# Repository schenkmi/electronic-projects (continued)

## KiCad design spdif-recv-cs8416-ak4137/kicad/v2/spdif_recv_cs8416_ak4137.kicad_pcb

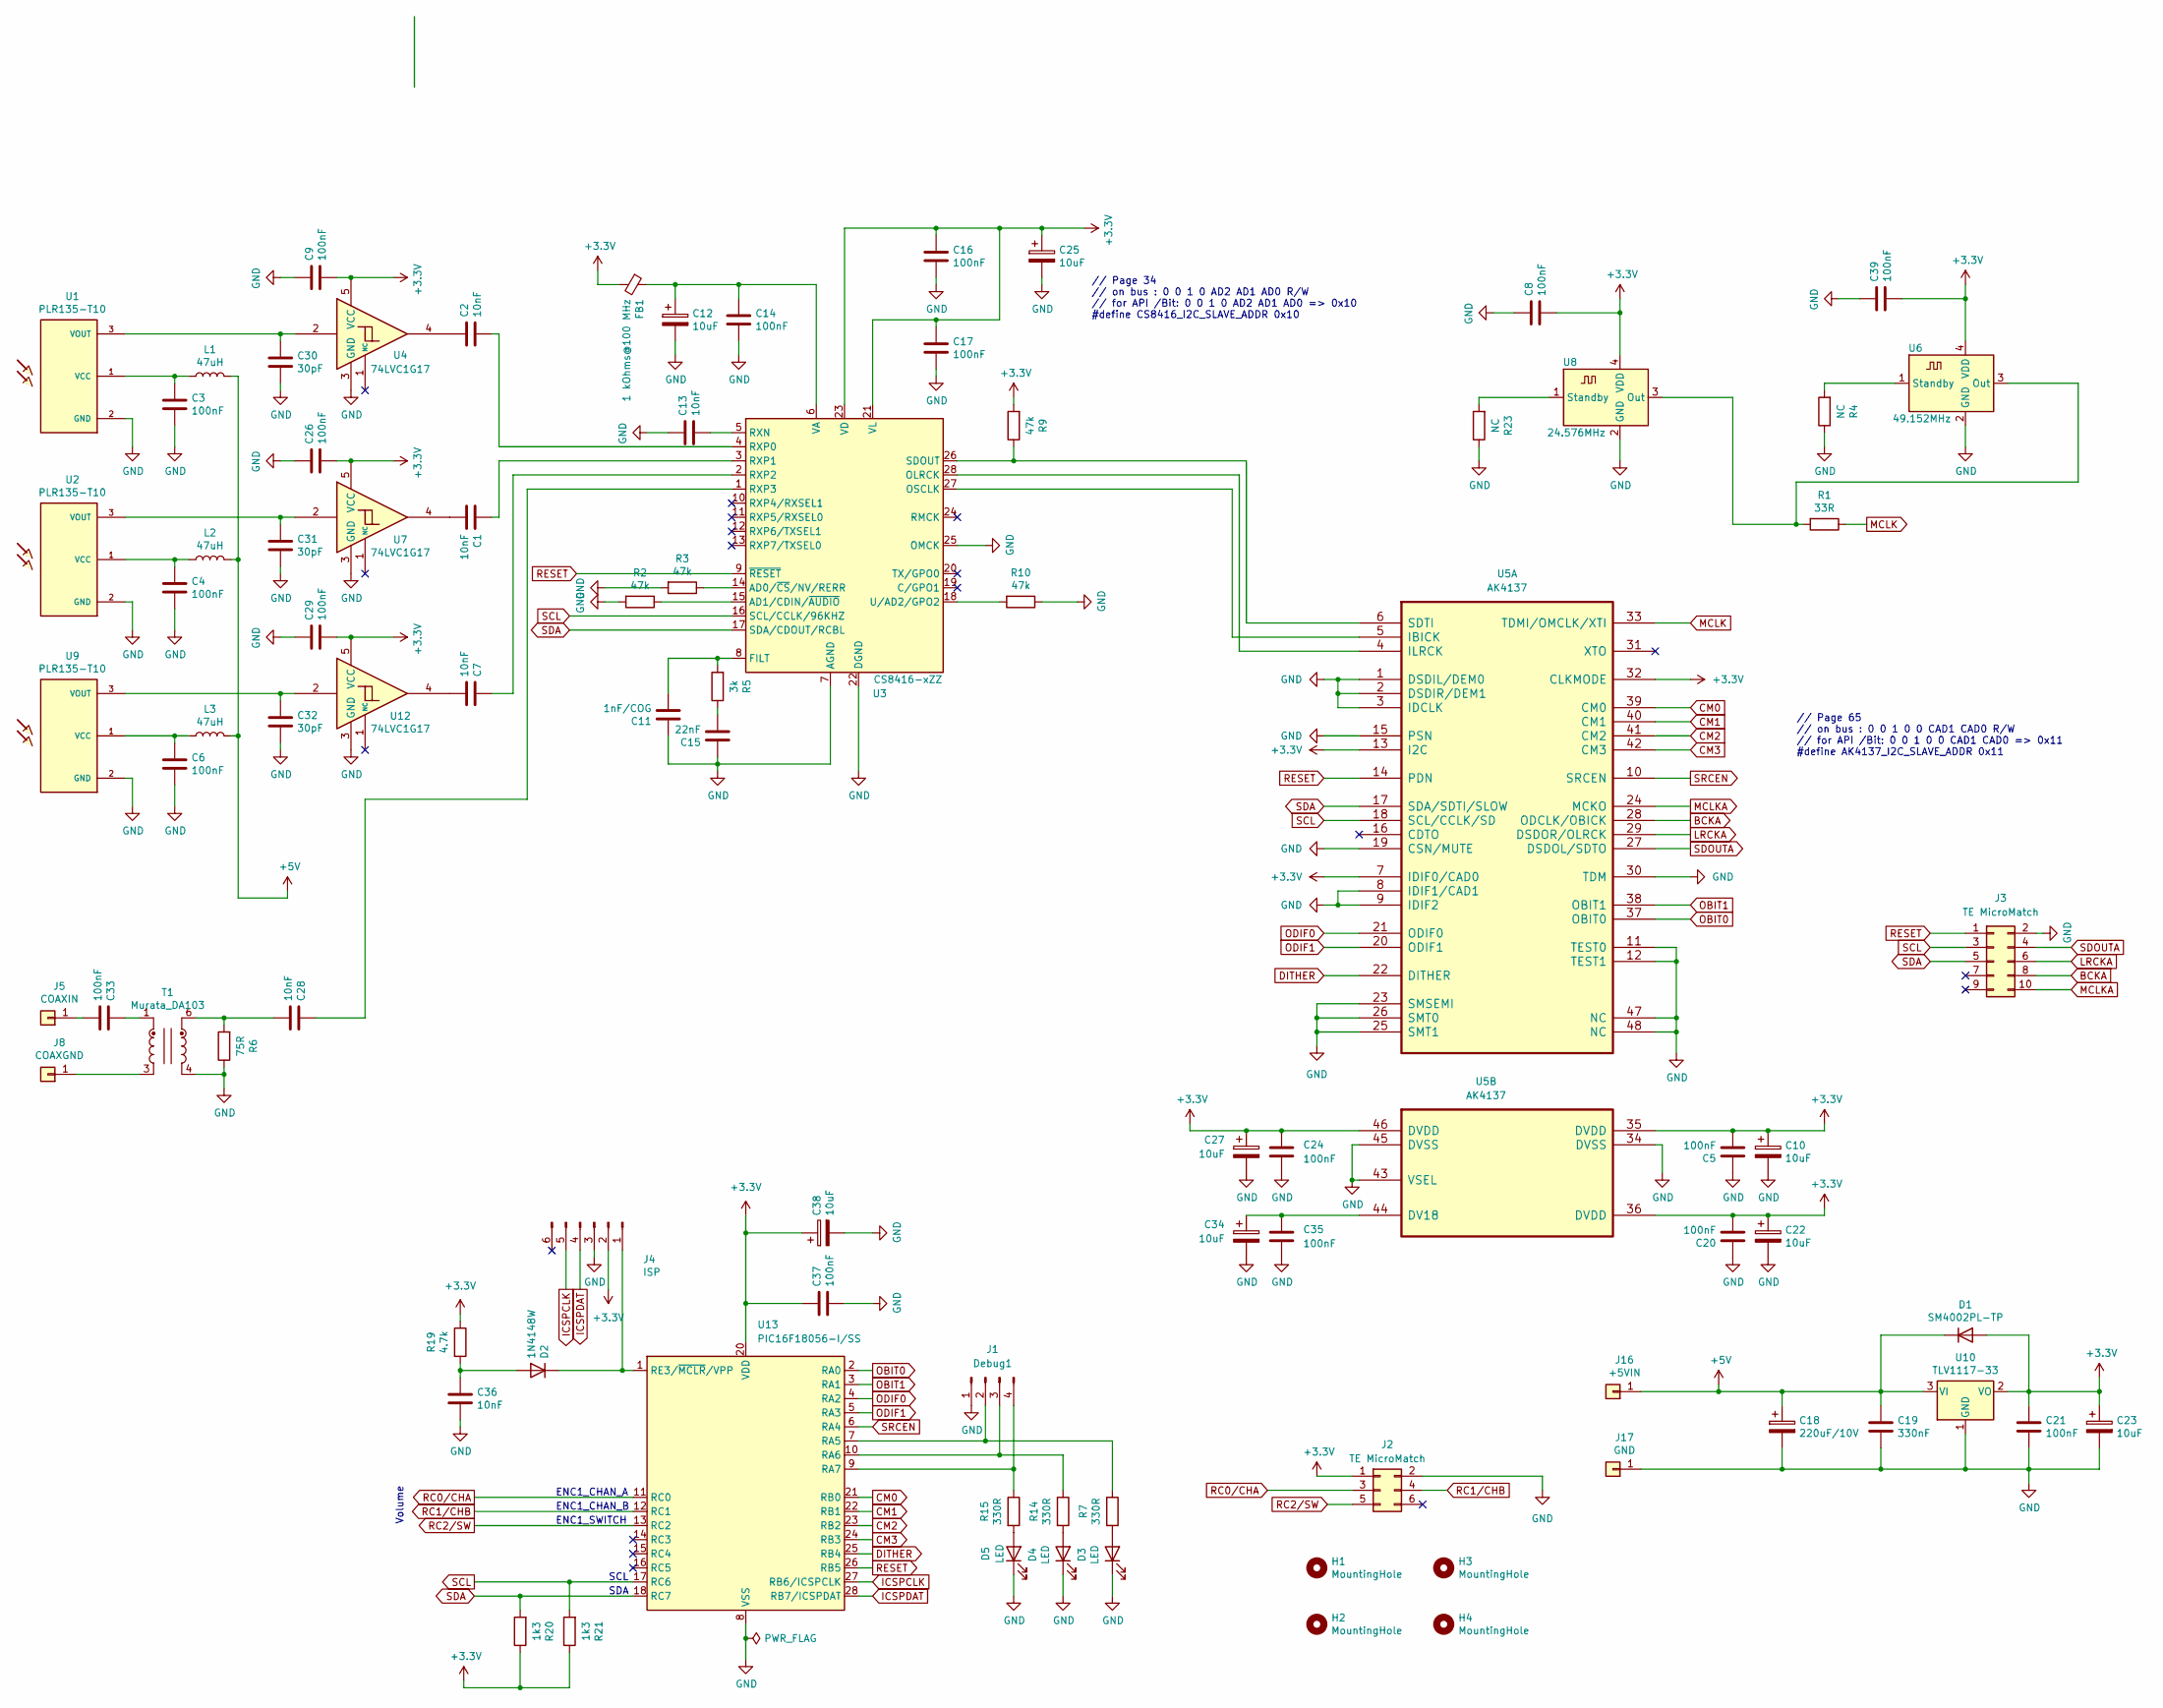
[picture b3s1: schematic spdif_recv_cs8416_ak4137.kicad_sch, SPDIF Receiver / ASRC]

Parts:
C1, C2, C7, C13, C28, C36: 10nF; C_0603_1608Metric_Pad1.08x0.95mm_HandSolder
C3, C4, C5, C6, C8, C9, C14, C16, C17, C20, C24, C26, C29, C33, C35, C37, C39: 100nF; C_0603_1608Metric_Pad1.08x0.95mm_HandSolder
C10, C12, C22, C23, C25, C27, C34, C38: 10uF; CP_EIA-2012-12_Kemet-R_Pad1.30x1.05mm_HandSolder
C11: 1nF/COG; C_0603_1608Metric_Pad1.08x0.95mm_HandSolder
C15: 22nF; C_0603_1608Metric_Pad1.08x0.95mm_HandSolder
C18: 220uF/10V; CP_Radial_D6.3mm_P2.50mm
C19: 330nF; C_0805_2012Metric_Pad1.18x1.45mm_HandSolder
C21: 100nF; C_0805_2012Metric_Pad1.18x1.45mm_HandSolder
C30, C31, C32: 30pF; C_0603_1608Metric_Pad1.08x0.95mm_HandSolder
D1: SM4002PL-TP; D_SOD-123F
D2: 1N4148W; D_SOD-123
D3, D4, D5: LED; LED_0603_1608Metric_Pad1.05x0.95mm_HandSolder
FB1: 1 kOhms@100 MHz; C_0603_1608Metric_Pad1.08x0.95mm_HandSolder
H1, H2, H3, H4: MountingHole; MountingHole_3.2mm_M3_Pad_Via
J1: Debug1; PinHeader_1x04_P2.54mm_Vertical
J2: TE MicroMatch; TE_Micro-MaTch_215079-6_2x03_P1.27mm_Vertical
J3: TE MicroMatch; TE_Micro-MaTch_1-215079-0_2x05_P1.27mm_Vertical
J4: ISP; PinHeader_1x06_P2.54mm_Vertical
J5: COAXIN; Pin_D1.0mm_L10.0mm
J8: COAXGND; Pin_D1.0mm_L10.0mm
J16: +5VIN; Pin_D1.0mm_L10.0mm
J17: GND; Pin_D1.0mm_L10.0mm
L1, L2, L3: 47uH; L_0805_2012Metric_Pad1.05x1.20mm_HandSolder
R1: 33R; R_0603_1608Metric_Pad0.98x0.95mm_HandSolder
R2, R3, R9, R10: 47k; R_0603_1608Metric_Pad0.98x0.95mm_HandSolder
R4, R23: NC; R_0603_1608Metric_Pad0.98x0.95mm_HandSolder
R5: 3k; R_0603_1608Metric_Pad0.98x0.95mm_HandSolder
R6: 75R; R_0603_1608Metric_Pad0.98x0.95mm_HandSolder
R7, R14, R15: 330R; R_0603_1608Metric_Pad0.98x0.95mm_HandSolder
R19: 4.7k; R_0603_1608Metric_Pad0.98x0.95mm_HandSolder
R20, R21: 1k3; R_0603_1608Metric_Pad0.98x0.95mm_HandSolder
T1: Murata_DA103; DA100J
U1, U2, U9: PLR135-T10; PLR135-T10_PLT133-T10W
U3: CS8416-xZZ; TSSOP-28_4.4x9.7mm_P0.65mm
U4, U7, U12: 74LVC1G17; SOT-23-5
U5: AK4137; LQFP-48_7x7mm_P0.5mm
U6: 49.152MHz; Oscillator_SMD_EuroQuartz_XO32-4Pin_3.2x2.5mm_HandSoldering
U8: 24.576MHz; Oscillator_SMD_EuroQuartz_XO32-4Pin_3.2x2.5mm_HandSoldering
U10: TLV1117-33; SOT-223-3_TabPin2
U13: PIC16F18056-I/SS; SSOP-28_5.3x10.2mm_P0.65mm

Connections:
+3.3V: C5.2, C8.1, C9.1, C10.1, C16.1, C17.1, C20.2, C21.1, C22.1, C23.1, C24.2, C25.1, C26.1, C27.1, C29.1, C37.1, C38.1, C39.1, D1.2 (A), FB1.2, J2.1, J4.2, R9.2, R19.1, R20.1, R21.1, U3.21 (VL), U3.23 (VD), U4.5 (VCC), U5.7 (IDIF0/CAD0), U5.13 (I2C), U5.32 (CLKMODE), U5.35 (DVDD), U5.36 (DVDD), U5.46 (DVDD), U6.4 (VDD), U7.5 (VCC), U8.4 (VDD), U10.2 (VO), U12.5 (VCC), U13.20 (VDD)
+5V: C18.1, C19.1, D1.1 (K), J16.1, L1.2, L2.2, L3.2, U10.3 (VI)
BCKA: J3.8, U5.28 (ODCLK/OBICK)
CM0: U5.39 (CM0), U13.21 (RB0)
CM1: U5.40 (CM1), U13.22 (RB1)
CM2: U5.41 (CM2), U13.23 (RB2)
CM3: U5.42 (CM3), U13.24 (RB3)
DITHER: U5.22 (DITHER), U13.25 (RB4)
GND: C3.1, C4.1, C5.1, C6.1, C8.2, C9.2, C10.2, C11.1, C12.2, C13.2, C14.2, C15.1, C16.2, C17.2, C18.2, C19.2, C20.1, C21.2, C22.2, C23.2, C24.1, C25.2, C26.2, C27.2, C29.2, C30.1, C31.1, C32.1, C34.2, C35.1, C36.2, C37.2, C38.2, C39.2, D3.1 (K), D4.1 (K), D5.1 (K), J1.1, J2.2, J3.2, J4.3, J17.1, R2.2, R3.2, R4.1, R6.1, R10.1, R23.1, T1.4, U1.2 (GND), U2.2 (GND), U3.7 (AGND), U3.22 (DGND), U3.25 (OMCK), U4.3 (GND), U5.1 (DSDIL/DEM0), U5.2 (DSDIR/DEM1), U5.3 (IDCLK), U5.8 (IDIF1/CAD1), U5.9 (IDIF2), U5.11 (TEST0), U5.12 (TEST1), U5.15 (PSN), U5.19 (CSN/MUTE), U5.23 (SMSEMI), U5.25 (SMT1), U5.26 (SMT0), U5.30 (TDM), U5.34 (DVSS), U5.43 (VSEL), U5.45 (DVSS), U5.47 (NC), U5.48 (NC), U6.2 (GND), U7.3 (GND), U8.2 (GND), U9.2 (GND), U10.1 (GND), U12.3 (GND), U13.8 (VSS), U13.19 (VSS)
ICSPCLK: J4.5, U13.27 (RB6/ICSPCLK)
ICSPDAT: J4.4, U13.28 (RB7/ICSPDAT)
LRCKA: J3.6, U5.29 (DSDOR/OLRCK)
MCLK: R1.1, U5.33 (TDMI/OMCLK/XTI)
MCLKA: J3.10, U5.24 (MCKO)
unnamed: C1.1, U7.4
unnamed: C2.2, U4.4
unnamed: C7.1, U12.4
unnamed: C15.2, R5.1
unnamed: C28.1, R6.2, T1.6
unnamed: C33.2, T1.1
unnamed: C36.1, D2.2 (A), R19.2
unnamed: D2.1 (K), J4.1, U13.1 (RE3/~MCLR/VPP)
unnamed: D3.2 (A), R7.2
unnamed: D4.2 (A), R14.2
unnamed: D5.2 (A), R15.2
unnamed: J1.2, R7.1, U13.7 (RA5)
unnamed: J1.3, R14.1, U13.10 (RA6)
unnamed: J1.4, R15.1, U13.9 (RA7)
unnamed: C33.1, J5.1
unnamed: J8.1, T1.3
unnamed: C3.2, L1.1, U1.1 (VCC)
unnamed: C30.2, U1.3 (VOUT), U4.2
unnamed: C4.2, L2.1, U2.1 (VCC)
unnamed: C31.2, U2.3 (VOUT), U7.2
unnamed: R3.1, U3.14 (AD0/~CS/NV/RERR)
unnamed: R2.1, U3.15 (AD1/CDIN/~AUDIO)
unnamed: C11.2, R5.2, U3.8 (FILT)
unnamed: U3.28 (OLRCK), U5.4 (ILRCK)
unnamed: U3.27 (OSCLK), U5.5 (IBICK)
unnamed: C13.1, U3.5 (RXN)
unnamed: C2.1, U3.4 (RXP0)
unnamed: C1.2, U3.3 (RXP1)
unnamed: C7.2, U3.2 (RXP2)
unnamed: C28.2, U3.1 (RXP3)
unnamed: R9.1, U3.26 (SDOUT), U5.6 (SDTI)
unnamed: R10.2, U3.18 (U/AD2/GPO2)
unnamed: C12.1, C14.1, FB1.1, U3.6 (VA)
unnamed: C34.1, C35.2, U5.44 (DV18)
unnamed: R1.2, U6.3 (Out), U8.3 (Out)
unnamed: R4.2, U6.1 (Standby)
unnamed: R23.2, U8.1 (Standby)
unnamed: C6.2, L3.1, U9.1 (VCC)
unnamed: C32.2, U9.3 (VOUT), U12.2
OBIT0: U5.37 (OBIT0), U13.2 (RA0)
OBIT1: U5.38 (OBIT1), U13.3 (RA1)
ODIF0: U5.21 (ODIF0), U13.4 (RA2)
ODIF1: U5.20 (ODIF1), U13.5 (RA3)
RC0/CHA: J2.3, U13.11 (RC0)
RC1/CHB: J2.4, U13.12 (RC1)
RC2/SW: J2.5, U13.13 (RC2)
RESET: J3.1, U3.9 (~RESET), U5.14 (PDN), U13.26 (RB5)
SCL: J3.3, R21.2, U3.16 (SCL/CCLK/96KHZ), U5.18 (SCL/CCLK/SD), U13.17 (RC6)
SDA: J3.5, R20.2, U3.17 (SDA/CDOUT/RCBL), U5.17 (SDA/SDTI/SLOW), U13.18 (RC7)
SDOUTA: J3.4, U5.27 (DSDOL/SDTO)
SRCEN: U5.10 (SRCEN), U13.6 (RA4)

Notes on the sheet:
// Page 65 // on bus : 0 0 1 0 0 CAD1 CAD0 R/W // for API /Bit: 0 0 1 0 0 CAD1 CAD0 => 0x11 #define AK4137_I2C_SLAVE_ADDR 0x11
ENC1_CHAN_A
SDA
// Page 34 // on bus : 0 0 1 0 AD2 AD1 AD0 R/W // for API /Bit: 0 0 1 0 AD2 AD1 AD0 => 0x10 #define CS8416_I2C_SLAVE_ADDR 0x10
Volume
SCL
ENC1_SWITCH
ENC1_CHAN_B

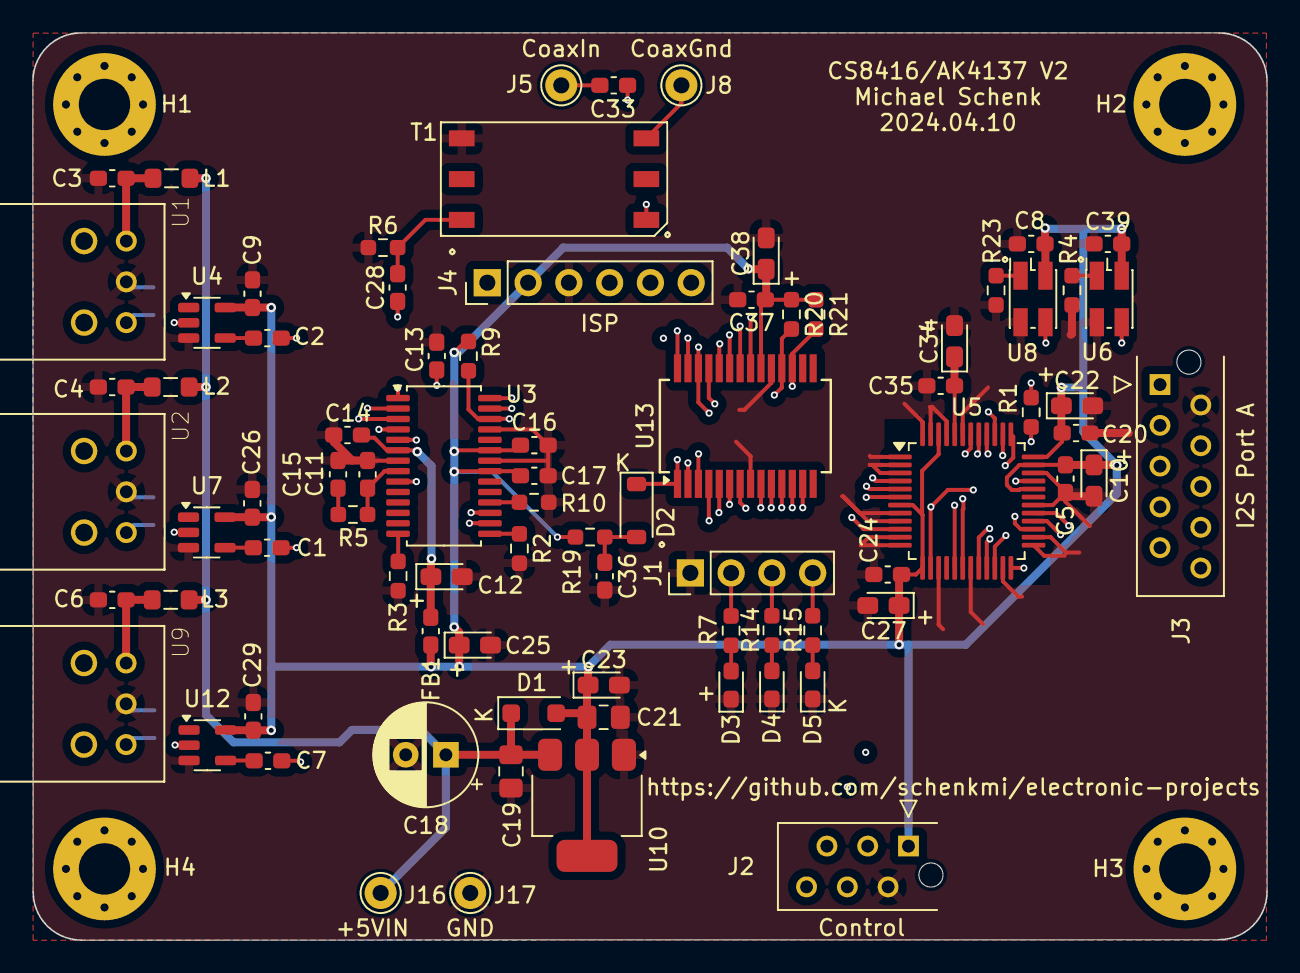
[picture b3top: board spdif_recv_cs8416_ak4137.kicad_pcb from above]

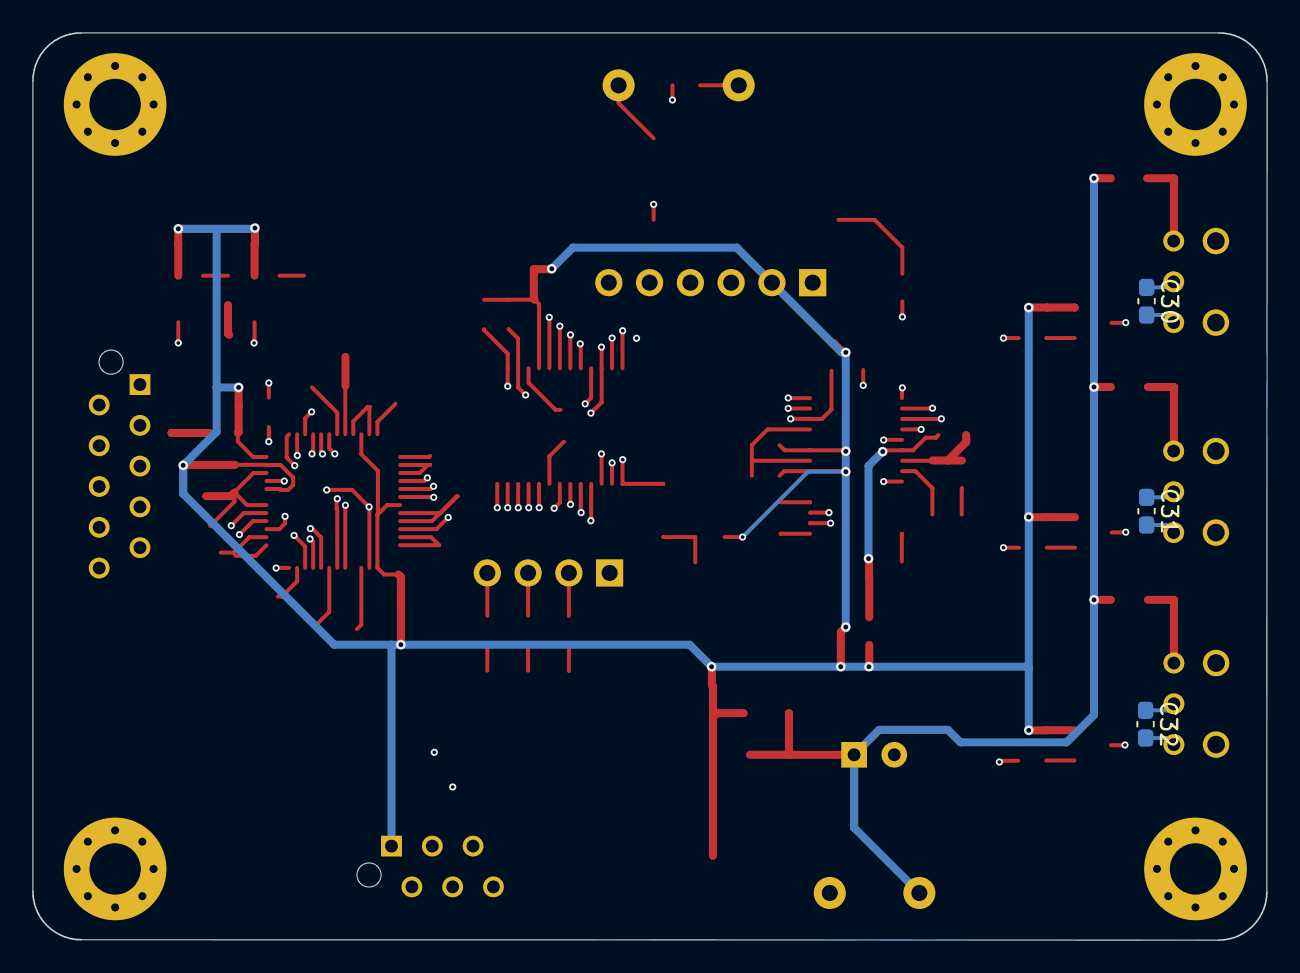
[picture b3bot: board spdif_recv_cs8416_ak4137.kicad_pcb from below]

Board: 4 copper layers, 76.9 x 56.5 mm, 88 parts (3 on the bottom side), 65 nets.
